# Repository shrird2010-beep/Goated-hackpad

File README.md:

# Goated-hackpad
The goated hackpad is my version of the hackpad that is going to be used to run some basic games. I have tried to follow the ASWD format with an extra key that i could use for other features. Currently it has 4 lights, 5 buttons, and an OLED that makes it that little bit better.
## Features
- 4 lights to give a rgb effect
- A big 0.91" OLED screen!
- kmk firmware! Control your mouse with this macropad
- A cool name!

| **Schematic** |
|---------------|

| **PCB** |
|---------|

I have used kicad for my schematic and PCB

| **Case** |
|---------------|

I have used onshape for this tutorial. The instructions on the website helped me tremendously along with the help of the slack and a couple of my friends.

| **Final Product** |

All of the components put together look like this!

## BOM

- 1x 3d printed case
- 1x Seeed XIAO RP2040 microcontroller
- 5x MX-Style switches
- 4x LEDs
- 1x 0.91 inch OLED display
- 5x DSA keycaps
- 4x 3x16mm screws
- 4x 3x5mx4mm heatset inserts

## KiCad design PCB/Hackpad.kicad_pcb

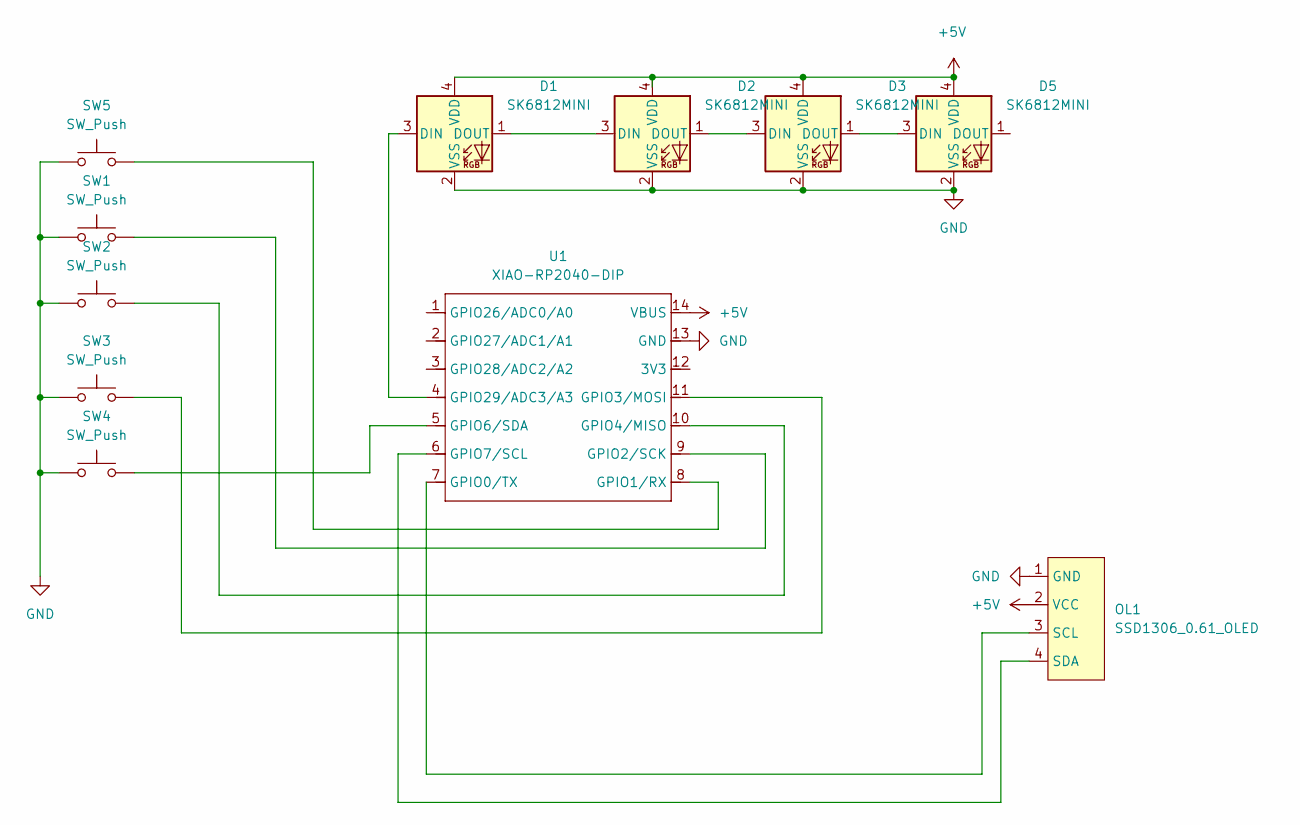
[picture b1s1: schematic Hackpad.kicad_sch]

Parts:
D1, D2, D3, D5: SK6812MINI; LED_SK6812MINI_PLCC4_3.5x3.5mm_P1.75mm
OL1: SSD1306_0.61_OLED; SSD1306-0.91-OLED-4pin-128x32
SW1, SW2, SW3, SW4, SW5: SW_Push; SW_Cherry_MX_1.00u_PCB
U1: XIAO-RP2040-DIP

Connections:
+5V: D1.4 (VDD), D2.4 (VDD), D3.4 (VDD), D5.4 (VDD), OL1.2 (VCC), U1.14 (VBUS)
GND: D1.2 (VSS), D2.2 (VSS), D3.2 (VSS), D5.2 (VSS), OL1.1 (GND), SW1.1, SW2.1, SW3.1, SW4.1, SW5.1, U1.13 (GND)
unnamed: D1.3 (DIN), U1.4 (GPIO29/ADC3/A3)
unnamed: D1.1 (DOUT), D2.3 (DIN)
unnamed: D2.1 (DOUT), D3.3 (DIN)
unnamed: D3.1 (DOUT), D5.3 (DIN)
unnamed: OL1.3 (SCL), U1.7 (GPIO0/TX)
unnamed: OL1.4 (SDA), U1.6 (GPIO7/SCL)
unnamed: SW5.2, U1.8 (GPIO1/RX)
unnamed: SW1.2, U1.9 (GPIO2/SCK)
unnamed: SW3.2, U1.11 (GPIO3/MOSI)
unnamed: SW2.2, U1.10 (GPIO4/MISO)
unnamed: SW4.2, U1.5 (GPIO6/SDA)

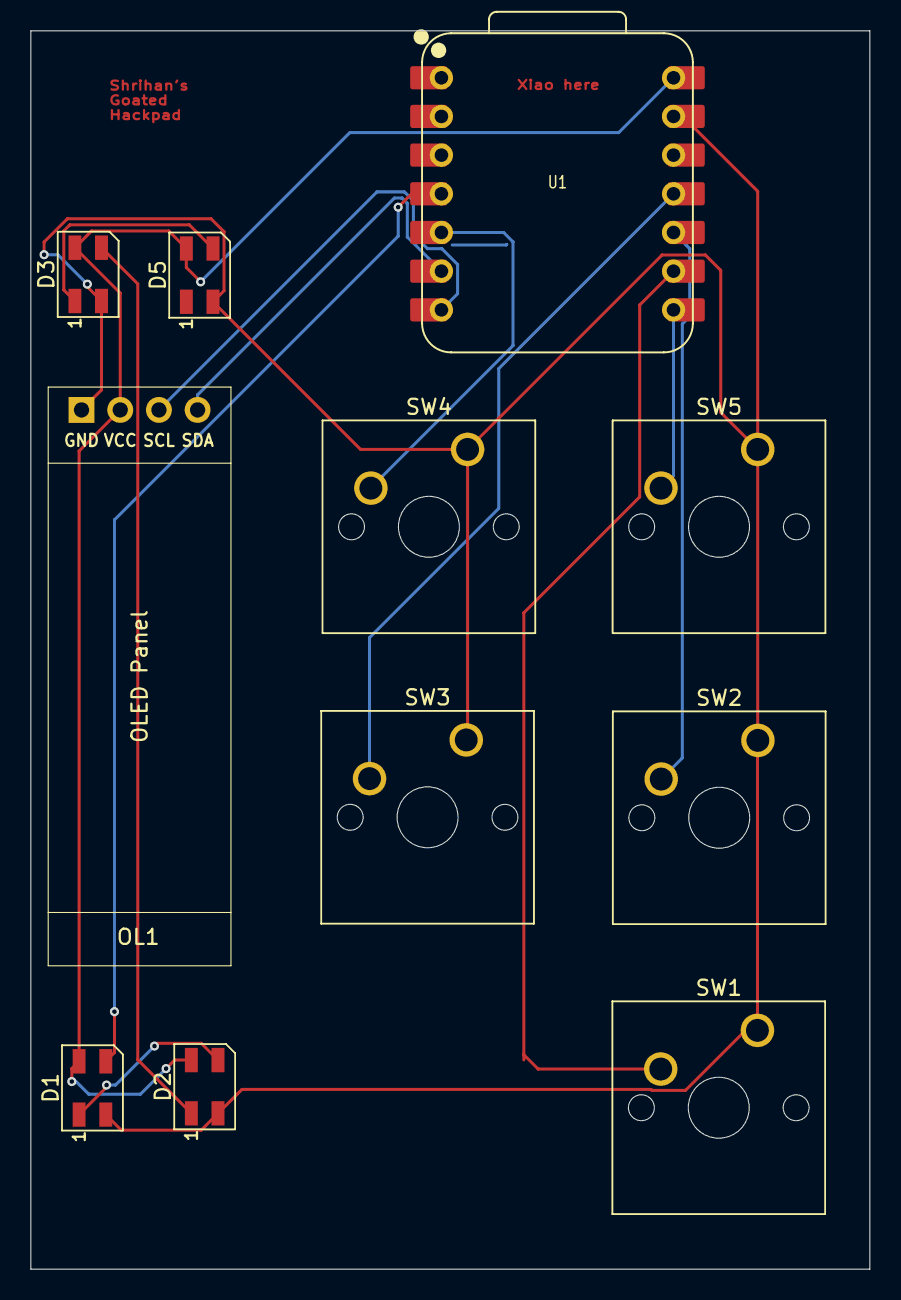
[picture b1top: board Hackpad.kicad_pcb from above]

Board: 2 copper layers, 55.1 x 81.3 mm, 11 parts (0 on the bottom side), 13 nets.

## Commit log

2025-11-26 Add CAD folder with Assembly 1.step
2025-11-26 Hackpad.kicad_pro
2025-11-26 Hackpad.kicad_sch
2025-11-26 Hackpad.kicad_pcb
2025-11-26 main.py
2025-11-27 Add files via upload
    Images
